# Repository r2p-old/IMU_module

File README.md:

template_module
===============

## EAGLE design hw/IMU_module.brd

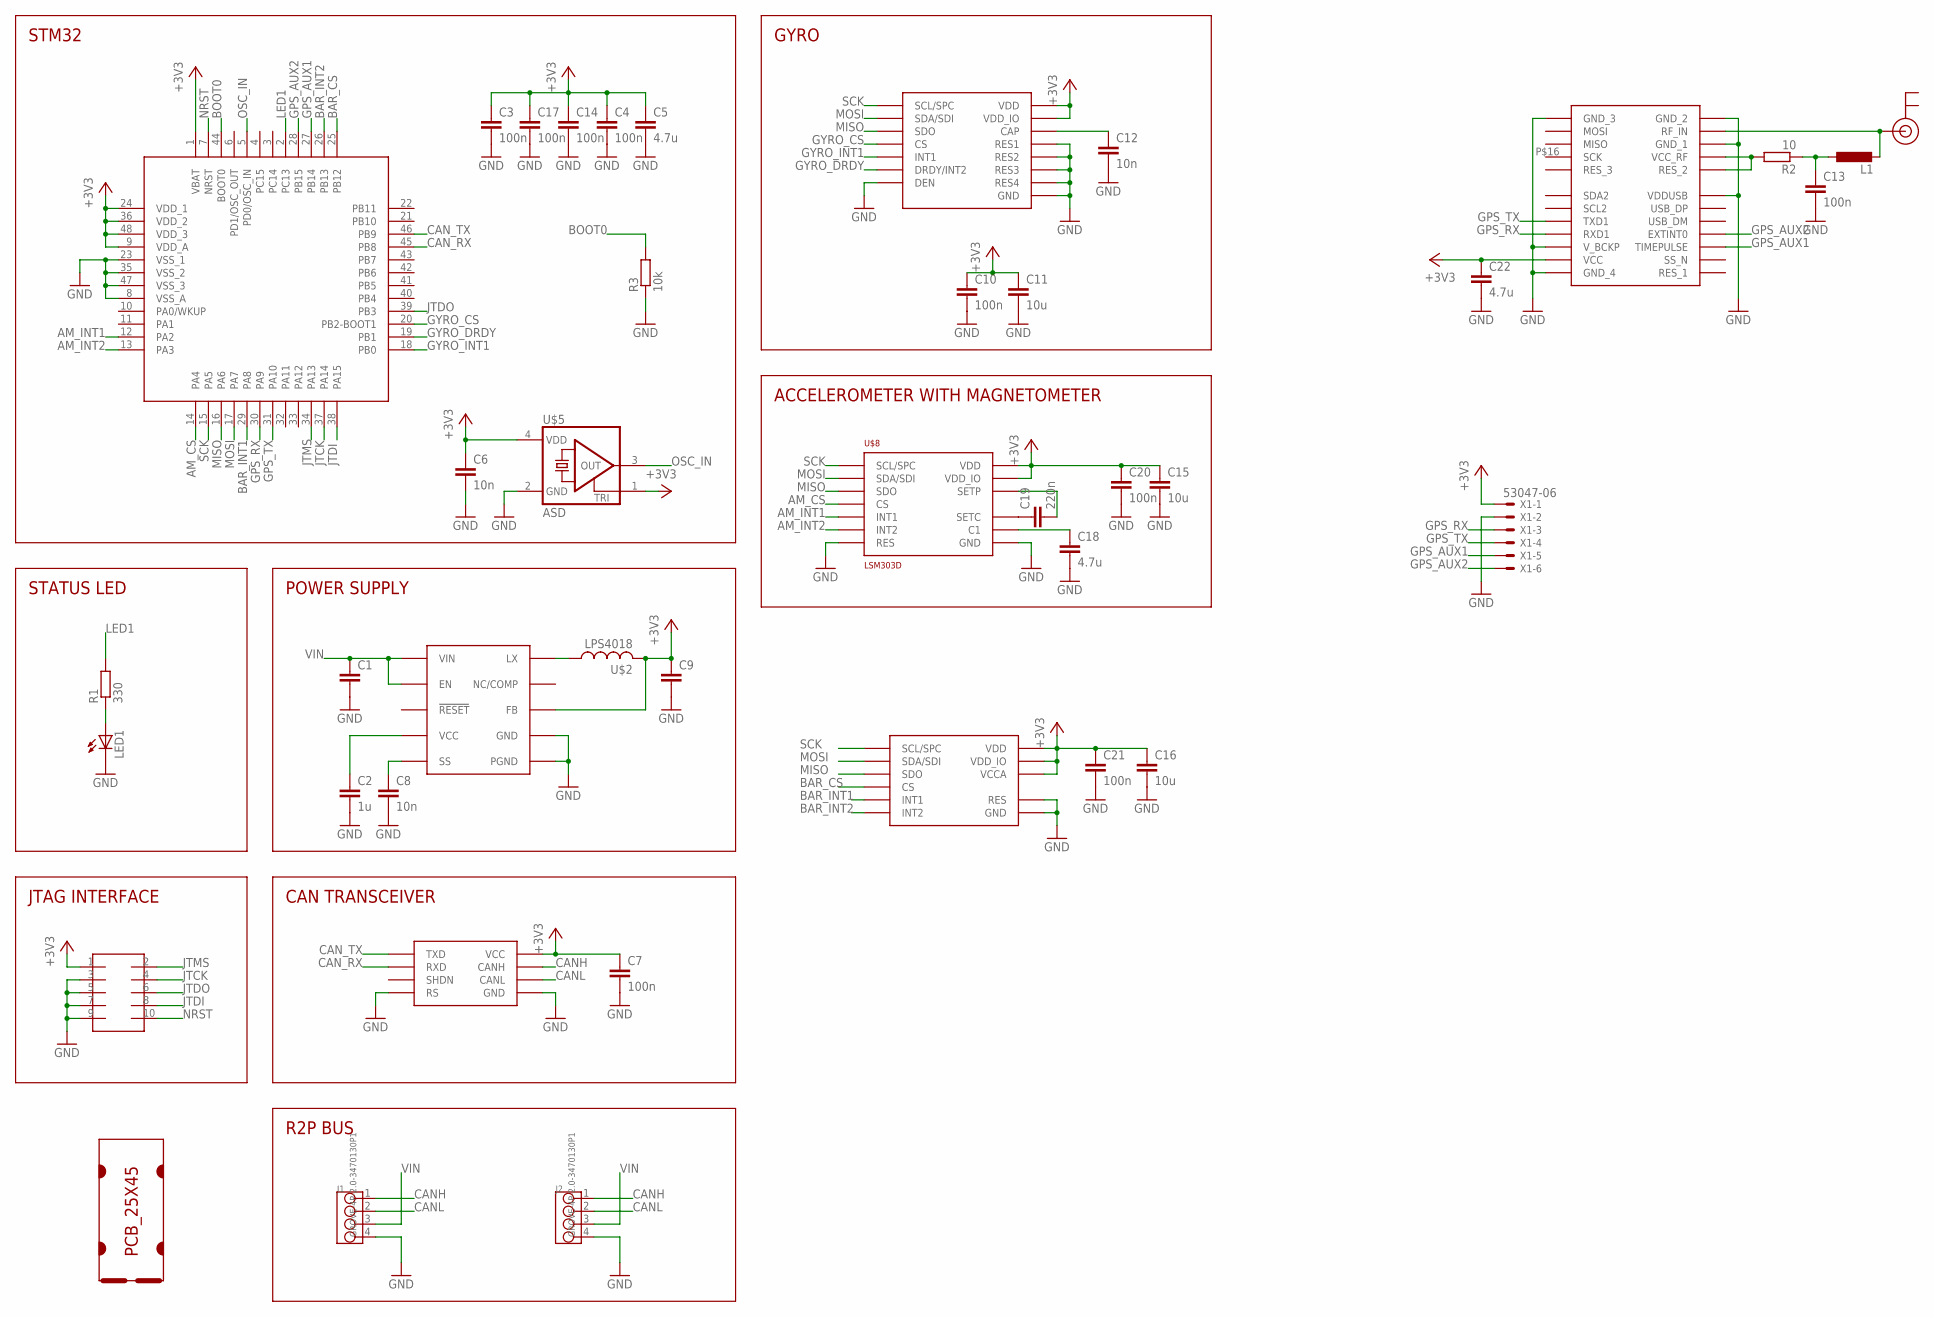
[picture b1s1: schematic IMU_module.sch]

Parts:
C1: C-EUC1206; C1206
C2: 1u; C0603
C3, C4, C7, C10, C13, C14, C17, C20, C21: 100n; C0603
C5, C18, C22: 4.7u; C0805
C6, C8, C12: 10n; C0603
C9: C-EUC0805; C0805
C11, C15, C16: 10u; C0805
C19: 220n; C0603
J1, J2: GROVE-4P-2.0-3470130P1; 4P-2.0
L1: L-EUL2012C; L2012C
LED1: LEDCHIPLED_0805; CHIPLED_0805
R1: 330; R0603
R2: 10; R0603
R3: 10k; R0603
SOT1: MAX3051EKA; SOT23-8L
U$1: PCB_25X45; 25X45
U$2: LPS4018
U$3: MAX17501; TDFN-10
U$4: FTSH-105TH; FTSH-105-TH
U$5: ASD; 2.5X2
U$6: STM32F103CXTX; LQFP48
U$7: L3GD20H; LGA16L
U$8: LSM303D; LGA16L
U$9: LPS331AP; LGA16L
U$10: NEO-6; NEO
U$11: U.FL
X1: 53047-06

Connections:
+3V3: C3.1, C4.1, C5.1, C6.1, C7.1, C9.1, C10.1, C11.1, C14.1, C15.1, C16.1, C17.1, C20.1, C21.1, C22.1, SOT1.3 (VCC), U$2.P$2 (2), U$3.P$5 (FB), U$4.1, U$5.1 (TRI), U$5.4 (VDD), U$6.1 (VBAT), U$6.9 (VDD_A), U$6.24 (VDD_1), U$6.36 (VDD_2), U$6.48 (VDD_3), U$7.P$1 (VDD_IO), U$7.P$16 (VDD), U$8.P$1 (VDD_IO), U$8.P$14 (VDD), U$9.P$1 (VDD_IO), U$9.P$14 (VDD), U$9.P$15 (VCCA), U$10.P$23 (VCC), X1.1
AM_CS: U$6.14 (PA4), U$8.P$8 (CS)
AM_INT1: U$6.12 (PA2), U$8.P$11 (INT1)
AM_INT2: U$6.13 (PA3), U$8.P$9 (INT2)
BAR_CS: U$6.25 (PB12), U$9.P$8 (CS)
BAR_INT1: U$6.29 (PA8), U$9.P$11 (INT1)
BAR_INT2: U$6.26 (PB13), U$9.P$9 (INT2)
BOOT0: R3.2, U$6.44 (BOOT0)
CANH: J1.1, J2.1, SOT1.7 (CANH)
CANL: J1.2, J2.2, SOT1.6 (CANL)
CAN_RX: SOT1.4 (RXD), U$6.45 (PB8)
CAN_TX: SOT1.1 (TXD), U$6.46 (PB9)
GND: C1.2, C2.2, C3.2, C4.2, C5.2, C6.2, C7.2, C8.2, C9.2, C10.2, C11.2, C12.2, C13.2, C14.2, C15.2, C16.2, C17.2, C18.2, C20.2, C21.2, C22.2, J1.4, J2.4, LED1.C, R3.1, SOT1.2 (GND), SOT1.8 (RS), U$3.P$1 (PGND), U$3.P$9 (GND), U$3.P$11 (PGND), U$4.3, U$4.5, U$4.7, U$4.9, U$5.2 (GND), U$6.8 (VSS_A), U$6.23 (VSS_1), U$6.35 (VSS_2), U$6.47 (VSS_3), U$7.P$8 (DEN), U$7.P$9 (RES1), U$7.P$10 (RES2), U$7.P$11 (RES3), U$7.P$12 (GND), U$7.P$13 (GND), U$7.P$15 (RES4), U$8.P$5 (GND), U$8.P$10 (RES), U$8.P$12 (GND), U$8.P$13 (GND), U$8.P$16 (GND), U$9.P$5 (GND), U$9.P$10 (RES), U$9.P$12 (GND), U$9.P$13 (GND), U$9.P$16 (GND), U$10.P$7 (VDDUSB), U$10.P$10 (GND_1), U$10.P$12 (GND_2), U$10.P$13 (GND_3), U$10.P$22 (V_BCKP), U$10.P$24 (GND_4), X1.2
GPS_AUX1: U$6.27 (PB14), U$10.P$3 (TIMEPULSE), X1.5
GPS_AUX2: U$6.28 (PB15), U$10.P$4 (EXTINT0), X1.6
GPS_RX: U$6.30 (PA9), U$10.P$21 (RXD1), X1.3
GPS_TX: U$6.31 (PA10), U$10.P$20 (TXD1), X1.4
GYRO_CS: U$6.20 (PB2-BOOT1), U$7.P$5 (CS)
GYRO_DRDY: U$6.19 (PB1), U$7.P$6 (DRDY/INT2)
GYRO_INT1: U$6.18 (PB0), U$7.P$7 (INT1)
JTCK: U$4.4, U$6.37 (PA14)
JTDI: U$4.8, U$6.38 (PA15)
JTDO: U$4.6, U$6.39 (PB3)
JTMS: U$4.2, U$6.34 (PA13)
LED1: R1.2, U$6.2 (PC13)
MISO: U$6.16 (PA6), U$7.P$4 (SDO), U$8.P$7 (SDO), U$9.P$7 (SDO)
MOSI: U$6.17 (PA7), U$7.P$3 (SDA/SDI), U$8.P$6 (SDA/SDI), U$9.P$6 (SDA/SDI)
unnamed: U$2.P$1 (1), U$3.P$10 (LX)
unnamed: C12.1, U$7.P$14 (CAP)
unnamed: LED1.A, R1.1
unnamed: C18.1, U$8.P$15 (C1)
unnamed: C19.1, U$8.P$2 (SETC)
unnamed: C2.1, U$3.P$4 (VCC)
unnamed: C8.1, U$3.P$6 (SS)
unnamed: C19.2, U$8.P$3 (SETP)
unnamed: L1.2, U$10.P$11 (RF_IN), U$11.P$3 (SIGNAL)
unnamed: C13.1, L1.1, R2.1
unnamed: R2.2, U$10.P$8 (RES_2), U$10.P$9 (VCC_RF)
NRST: U$4.10, U$6.7 (NRST)
OSC_IN: U$5.3 (OUT), U$6.5 (PD0/OSC_IN)
SCK: U$6.15 (PA5), U$7.P$2 (SCL/SPC), U$8.P$4 (SCL/SPC), U$9.P$4 (SCL/SPC)
VIN: C1.1, J1.3, J2.3, U$3.P$2 (VIN), U$3.P$3 (EN)

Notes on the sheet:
STM32
STATUS LED
JTAG INTERFACE
POWER SUPPLY
CAN TRANSCEIVER
R2P BUS
ACCELEROMETER WITH MAGNETOMETER
GYRO

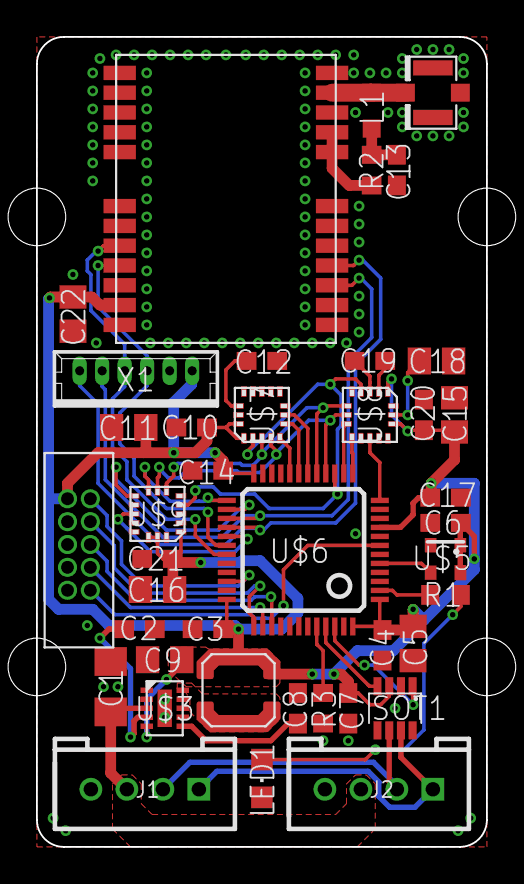
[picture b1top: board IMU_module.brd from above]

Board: 2 copper layers, 25.0 x 45.0 mm, 42 parts (0 on the bottom side), 42 nets.

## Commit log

2014-05-29 added MEMS datasheets to doc foder
2014-05-29 added TIMEPULSE and INT0 signals
2014-06-04 updated GPS connector to have Vcc on pin 1
2014-06-23 Added makefile for quicker gerber generation
2014-06-24 added PNG of board layout
2014-08-25 up to date
2014-12-16 small fixes for production
2014-12-16 moved LSM303D interrupt lines
2014-12-16 small fixes
2014-12-29 approved DRC false errors
2015-01-08 added logo to bottom silkscreen
2015-01-13 minor fixes for manufacturing
2015-01-22 added assembly PDF generation
2015-03-15 Renamed gyro DRDY signal and updated makefile

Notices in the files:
parts and their libraries:
SparkFun: Licensing: CC v3.0 Share-Alike You are welcome to use this library for commercial purposes.
